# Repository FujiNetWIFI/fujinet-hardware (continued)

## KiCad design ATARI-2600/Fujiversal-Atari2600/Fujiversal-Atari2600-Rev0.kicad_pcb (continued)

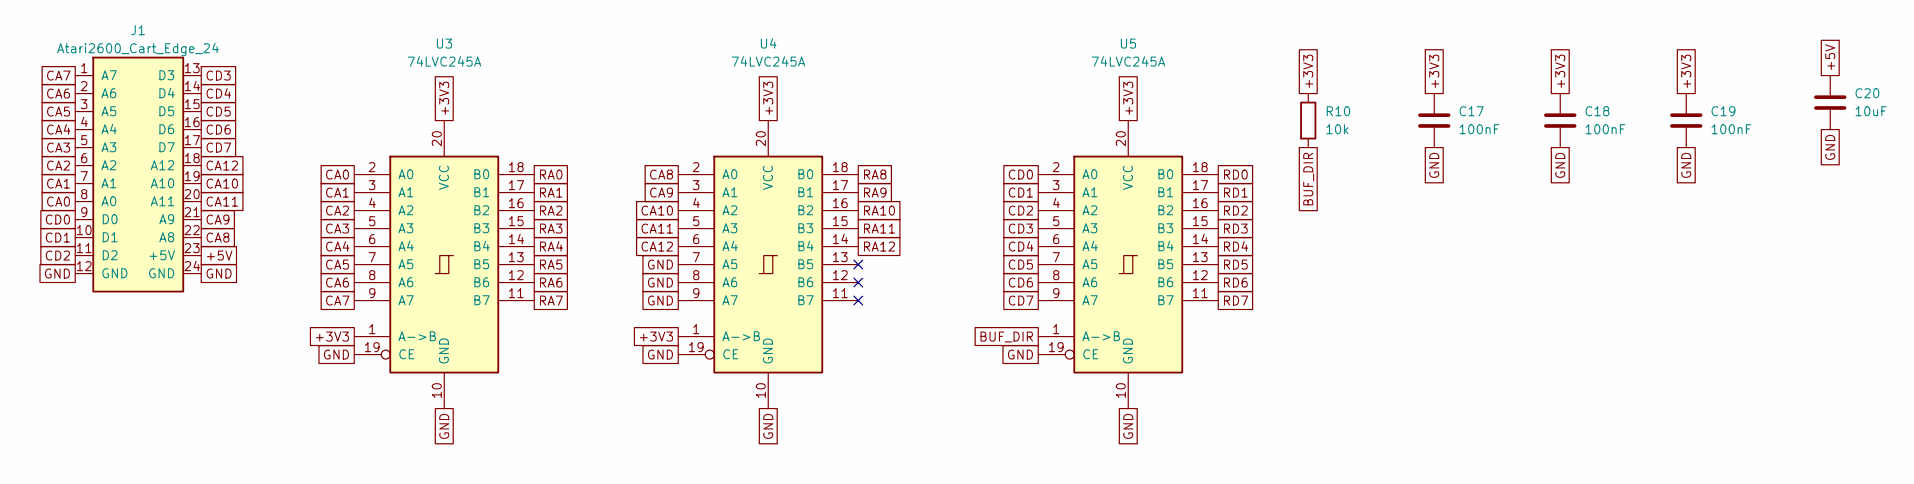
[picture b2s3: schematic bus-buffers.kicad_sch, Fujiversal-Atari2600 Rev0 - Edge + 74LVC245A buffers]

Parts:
C17, C18, C19: 100nF; C_0603_1608Metric; MPN CC0603KRX7R9BB104; LCSC C14663
C20: 10uF; C_0603_1608Metric; MPN CL10A106KP8NNNC; LCSC C19702
J1: Atari2600_Cart_Edge_24
R10: 10k; R_0603_1608Metric; MPN 0603WAF1002T5E; LCSC C25804
U3, U4, U5: 74LVC245A; TSSOP-20_4.4x6.5mm_P0.65mm; MPN 74LVC245APW,118; LCSC C6082

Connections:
+3V3: C17.1, C18.1, C19.1, R10.1, U3.1 (A->B), U3.20 (VCC), U4.1 (A->B), U4.20 (VCC), U5.20 (VCC); also elsewhere on the board
+5V: C20.1, J1.23 (+5V); also elsewhere on the board
BUF_DIR: R10.2, U5.1 (A->B); also elsewhere on the board
CA0: J1.8 (A0), U3.2 (A0)
CA1: J1.7 (A1), U3.3 (A1)
CA2: J1.6 (A2), U3.4 (A2)
CA3: J1.5 (A3), U3.5 (A3)
CA4: J1.4 (A4), U3.6 (A4)
CA5: J1.3 (A5), U3.7 (A5)
CA6: J1.2 (A6), U3.8 (A6)
CA7: J1.1 (A7), U3.9 (A7)
CA8: J1.22 (A8), U4.2 (A0)
CA9: J1.21 (A9), U4.3 (A1)
CA10: J1.19 (A10), U4.4 (A2)
CA11: J1.20 (A11), U4.5 (A3)
CA12: J1.18 (A12), U4.6 (A4)
CD0: J1.9 (D0), U5.2 (A0)
CD1: J1.10 (D1), U5.3 (A1)
CD2: J1.11 (D2), U5.4 (A2)
CD3: J1.13 (D3), U5.5 (A3)
CD4: J1.14 (D4), U5.6 (A4)
CD5: J1.15 (D5), U5.7 (A5)
CD6: J1.16 (D6), U5.8 (A6)
CD7: J1.17 (D7), U5.9 (A7)
GND: C17.2, C18.2, C19.2, C20.2, J1.12 (GND), J1.24 (GND), U3.10 (GND), U3.19 (CE), U4.7 (A5), U4.8 (A6), U4.9 (A7), U4.10 (GND), U4.19 (CE), U5.10 (GND), U5.19 (CE); also elsewhere on the board
RA0: U3.18 (B0); also elsewhere on the board
RA1: U3.17 (B1); also elsewhere on the board
RA2: U3.16 (B2); also elsewhere on the board
RA3: U3.15 (B3); also elsewhere on the board
RA4: U3.14 (B4); also elsewhere on the board
RA5: U3.13 (B5); also elsewhere on the board
RA6: U3.12 (B6); also elsewhere on the board
RA7: U3.11 (B7); also elsewhere on the board
RA8: U4.18 (B0); also elsewhere on the board
RA9: U4.17 (B1); also elsewhere on the board
RA10: U4.16 (B2); also elsewhere on the board
RA11: U4.15 (B3); also elsewhere on the board
RA12: U4.14 (B4); also elsewhere on the board
RD0: U5.18 (B0); also elsewhere on the board
RD1: U5.17 (B1); also elsewhere on the board
RD2: U5.16 (B2); also elsewhere on the board
RD3: U5.15 (B3); also elsewhere on the board
RD4: U5.14 (B4); also elsewhere on the board
RD5: U5.13 (B5); also elsewhere on the board
RD6: U5.12 (B6); also elsewhere on the board
RD7: U5.11 (B7); also elsewhere on the board

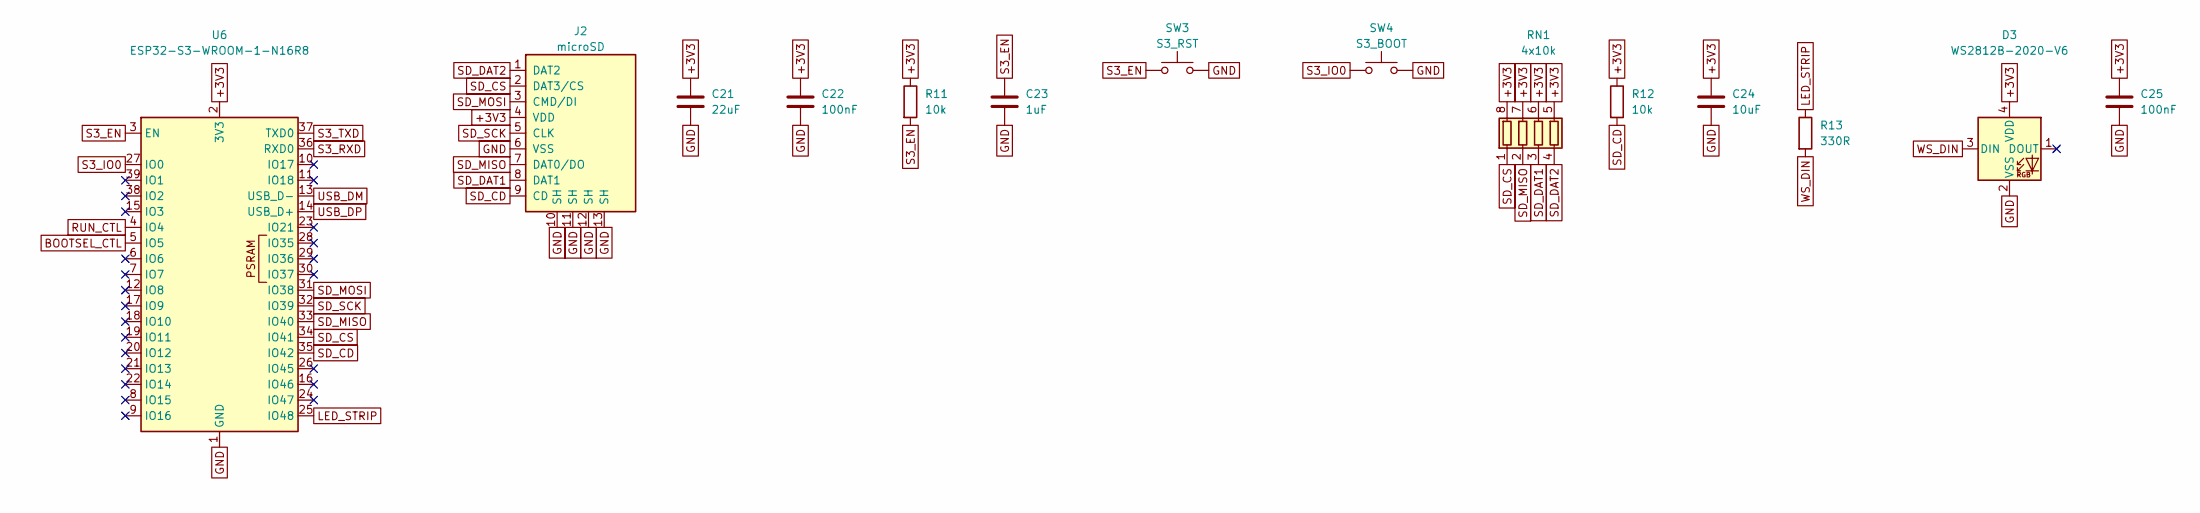
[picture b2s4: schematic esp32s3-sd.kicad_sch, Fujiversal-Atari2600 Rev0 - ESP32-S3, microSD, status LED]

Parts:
C21: 22uF; C_0805_2012Metric; MPN CL21A226MAQNNNE; LCSC C45783
C22, C25: 100nF; C_0603_1608Metric; MPN CC0603KRX7R9BB104; LCSC C14663
C23: 1uF; C_0603_1608Metric; MPN CL10A105KB8NNNC; LCSC C15849
C24: 10uF; C_0603_1608Metric; MPN CL10A106KP8NNNC; LCSC C19702
D3: WS2812B-2020-V6; LED_WS2812B-2020_PLCC4_2.0x2.0mm; MPN WS2812B-2020-V6; LCSC C52917434
J2: microSD; TF-SMD_TF-015; MPN TF-015; LCSC C113206
R11, R12: 10k; R_0603_1608Metric; MPN 0603WAF1002T5E; LCSC C25804
R13: 330R; R_0603_1608Metric; MPN 0603WAF3300T5E; LCSC C23138
RN1: 4x10k; R_Array_Convex_4x0603; MPN 4D03WGJ0103T5E; LCSC C29718
SW3: S3_RST; SW_SPST_TL3342; MPN TL3342F160QG; LCSC C2886898
SW4: S3_BOOT; SW_SPST_TL3342; MPN TL3342F160QG; LCSC C2886898
U6: ESP32-S3-WROOM-1-N16R8; ESP32-S3-WROOM-1; MPN ESP32-S3-WROOM-1-N16R8; LCSC C2913202

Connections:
+3V3: C21.1, C22.1, C24.1, C25.1, D3.4 (VDD), J2.4 (VDD), R11.1, R12.1, RN1.5 (R4.2), RN1.6 (R3.2), RN1.7 (R2.2), RN1.8 (R1.2), U6.2 (3V3); also elsewhere on the board
BOOTSEL_CTL: U6.5 (IO5); also elsewhere on the board
GND: C21.2, C22.2, C23.2, C24.2, C25.2, D3.2 (VSS), J2.6 (VSS), J2.10 (SH), J2.11 (SH), J2.12 (SH), J2.13 (SH), SW3.2, SW4.2, U6.1 (GND), U6.40 (GND), U6.41 (GND); also elsewhere on the board
LED_STRIP: R13.1, U6.25 (IO48)
RUN_CTL: U6.4 (IO4); also elsewhere on the board
S3_EN: C23.1, R11.2, SW3.1, U6.3 (EN); also elsewhere on the board
S3_IO0: SW4.1, U6.27 (IO0); also elsewhere on the board
S3_RXD: U6.36 (RXD0); also elsewhere on the board
S3_TXD: U6.37 (TXD0); also elsewhere on the board
SD_CD: J2.9 (CD), R12.2, U6.35 (IO42)
SD_CS: J2.2 (DAT3/CS), RN1.1 (R1.1), U6.34 (IO41)
SD_DAT1: J2.8 (DAT1), RN1.3 (R3.1)
SD_DAT2: J2.1 (DAT2), RN1.4 (R4.1)
SD_MISO: J2.7 (DAT0/DO), RN1.2 (R2.1), U6.33 (IO40)
SD_MOSI: J2.3 (CMD/DI), U6.31 (IO38)
SD_SCK: J2.5 (CLK), U6.32 (IO39)
USB_DM: U6.13 (USB_D-); also elsewhere on the board
USB_DP: U6.14 (USB_D+); also elsewhere on the board
WS_DIN: D3.3 (DIN), R13.2

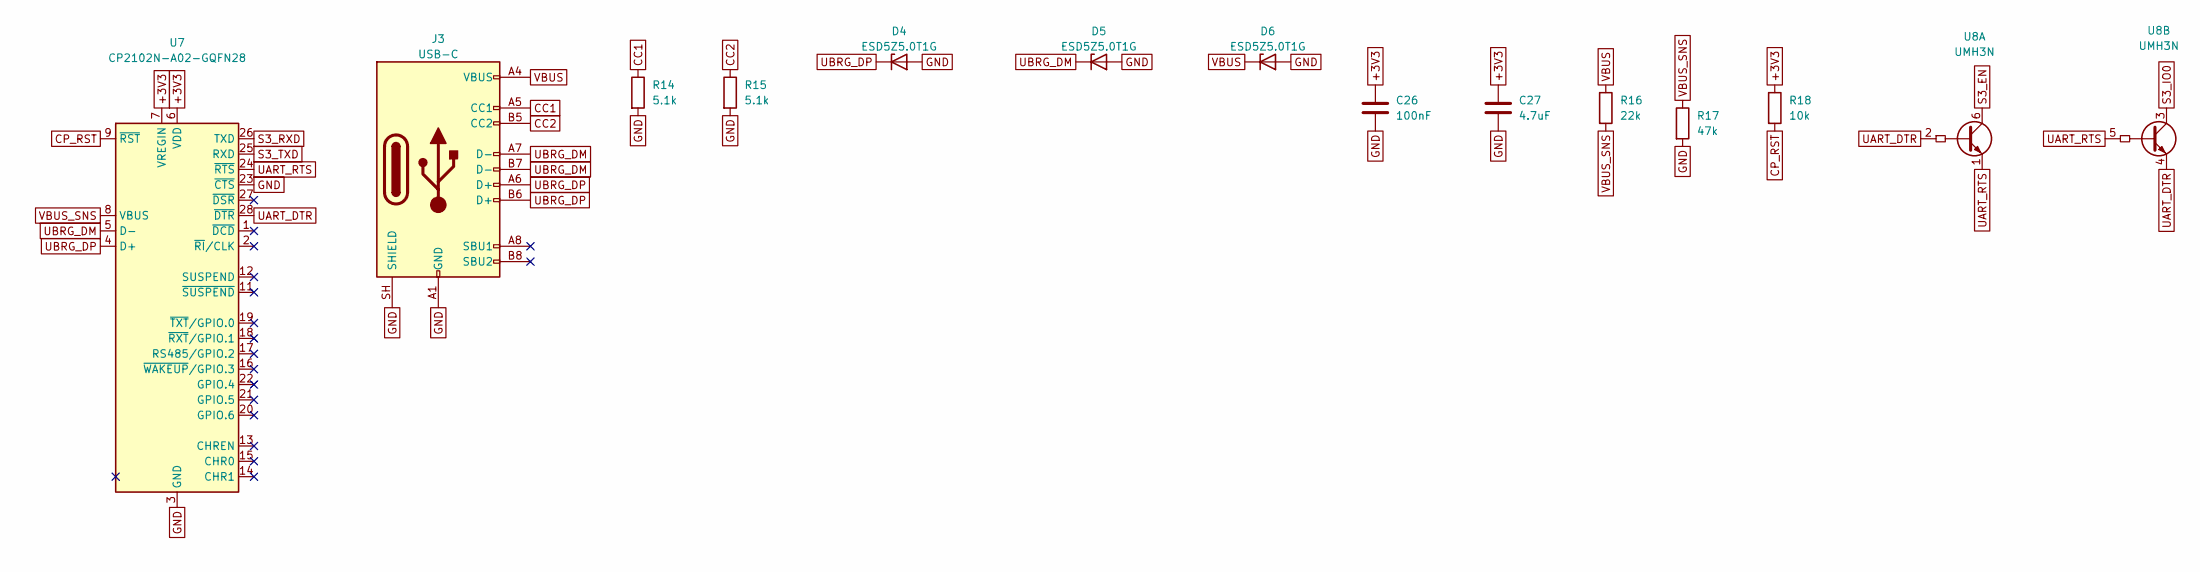
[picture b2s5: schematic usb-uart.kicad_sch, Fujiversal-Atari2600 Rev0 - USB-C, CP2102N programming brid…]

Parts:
C26: 100nF; C_0603_1608Metric; MPN CC0603KRX7R9BB104; LCSC C14663
C27: 4.7uF; C_0603_1608Metric; MPN CL10A475KO8NNNC; LCSC C19666
D4, D5, D6: ESD5Z5.0T1G; D_SOD-523; MPN ESD5Z5.0T1G; LCSC C82044
J3: USB-C; USB_C_Receptacle_HRO_TYPE-C-31-M-12; MPN TYPE-C-31-M-12; LCSC C165948
R14, R15: 5.1k; R_0603_1608Metric; MPN 0603WAF5101T5E; LCSC C23186
R16: 22k; R_0603_1608Metric; MPN 0603WAF2202T5E; LCSC C31850
R17: 47k; R_0603_1608Metric; MPN 0603WAF4702T5E; LCSC C25819
R18: 10k; R_0603_1608Metric; MPN 0603WAF1002T5E; LCSC C25804
U7: CP2102N-A02-GQFN28; QFN-28-1EP_5x5mm_P0.5mm_EP3.35x3.35mm; MPN CP2102N-A02-GQFN28R; LCSC C964632
U8: UMH3N; SOT-363_SC-70-6; MPN UMH3N; LCSC C62892

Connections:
+3V3: C26.1, C27.1, R18.1, U7.6 (VDD), U7.7 (VREGIN); also elsewhere on the board
CC1: J3.A5 (CC1), R14.1
CC2: J3.B5 (CC2), R15.1
CP_RST: R18.2, U7.9 (~RST)
GND: C26.2, C27.2, D4.2 (A), D5.2 (A), D6.2 (A), J3.A1 (GND), J3.A12 (GND), J3.B1 (GND), J3.B12 (GND), J3.SH (SHIELD), R14.2, R15.2, R17.2, U7.3 (GND), U7.23 (~CTS), U7.29 (GND); also elsewhere on the board
S3_EN: U8.6 (C1); also elsewhere on the board
S3_IO0: U8.3 (C2); also elsewhere on the board
S3_RXD: U7.26 (TXD); also elsewhere on the board
S3_TXD: U7.25 (RXD); also elsewhere on the board
UART_DTR: U7.28 (~DTR), U8.2 (B1), U8.4 (E2)
UART_RTS: U7.24 (~RTS), U8.1 (E1), U8.5 (B2)
UBRG_DM: D5.1 (K), J3.A7 (D-), J3.B7 (D-), U7.5 (D-)
UBRG_DP: D4.1 (K), J3.A6 (D+), J3.B6 (D+), U7.4 (D+)
VBUS: D6.1 (K), J3.A4 (VBUS), J3.A9 (VBUS), J3.B4 (VBUS), J3.B9 (VBUS), R16.1; also elsewhere on the board
VBUS_SNS: R16.2, R17.1, U7.8 (VBUS)

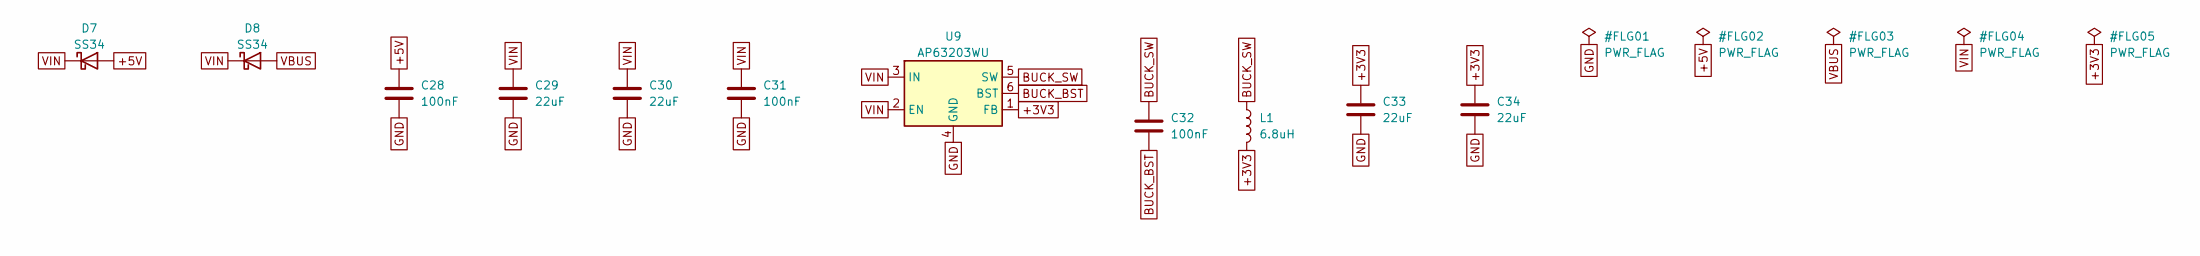
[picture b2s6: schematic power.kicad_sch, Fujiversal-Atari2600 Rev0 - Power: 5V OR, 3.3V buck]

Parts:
C28, C31, C32: 100nF; C_0603_1608Metric; MPN CC0603KRX7R9BB104; LCSC C14663
C29, C30, C33, C34: 22uF; C_0805_2012Metric; MPN CL21A226MAQNNNE; LCSC C45783
D7, D8: SS34; D_SMA; MPN SS34; LCSC C8678
L1: 6.8uH; L_Sunlord_SWPA4030S; MPN SWPA4030S6R8MT; LCSC C62684
U9: AP63203WU; TSOT-23-6; MPN AP63203WU-7; LCSC C780769

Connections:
+3V3: C33.1, C34.1, L1.2, U9.1 (FB); also elsewhere on the board
+5V: C28.1, D7.2 (A); also elsewhere on the board
BUCK_BST: C32.2, U9.6 (BST)
BUCK_SW: C32.1, L1.1, U9.5 (SW)
GND: C28.2, C29.2, C30.2, C31.2, C33.2, C34.2, U9.4 (GND); also elsewhere on the board
VBUS: D8.2 (A); also elsewhere on the board
VIN: C29.1, C30.1, C31.1, D7.1 (K), D8.1 (K), U9.2 (EN), U9.3 (IN)

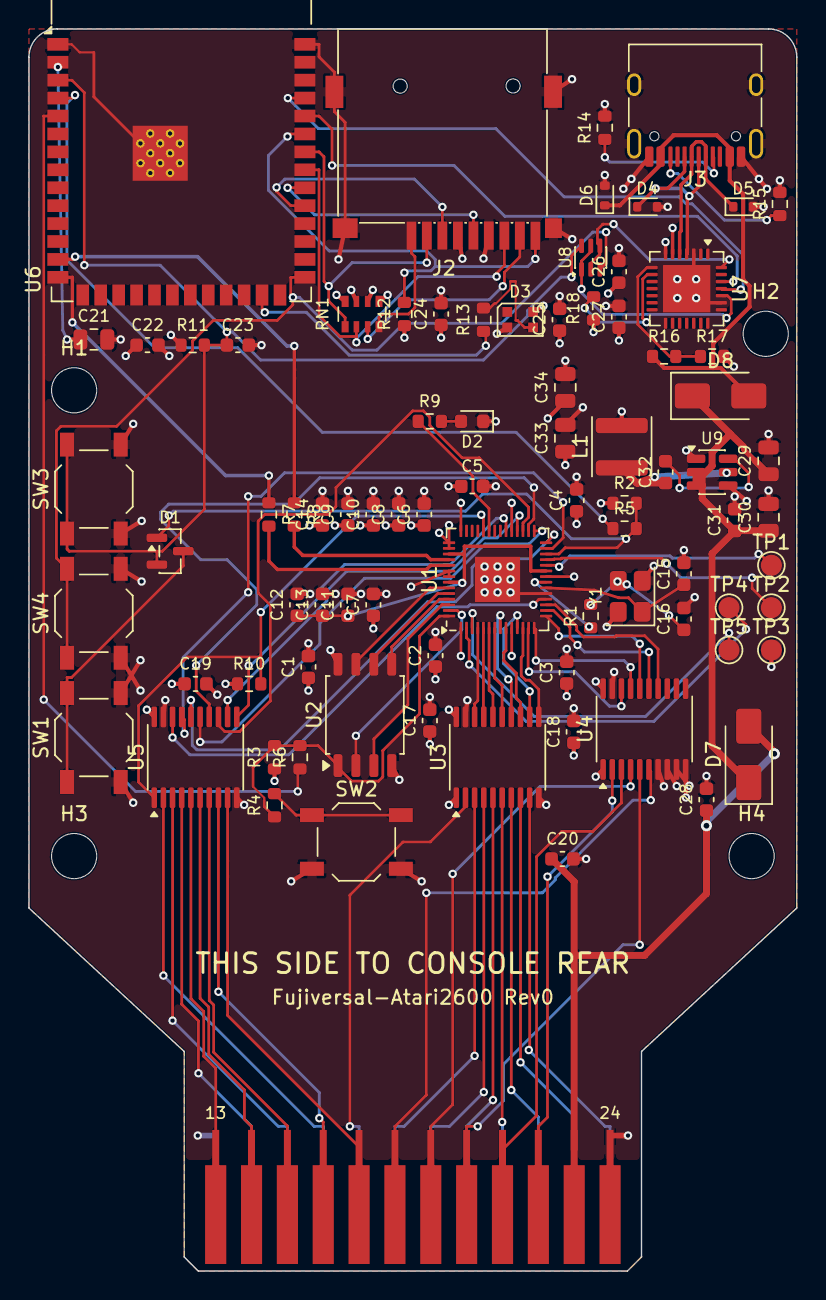
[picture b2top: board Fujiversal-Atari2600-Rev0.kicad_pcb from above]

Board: 4 copper layers, 54.4 x 88.0 mm, 88 parts (0 on the bottom side), 96 nets.

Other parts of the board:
H1, H2, H3, H4: M3; MountingHole_3.2mm_NPTH

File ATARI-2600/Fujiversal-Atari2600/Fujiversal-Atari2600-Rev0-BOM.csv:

"Refs","Value","Footprint","MPN","LCSC","Description","DNP"
"C1,C2,C3,C4,C5,C6,C7,C8,C9,C12,C13,C17,C18,C19,C22,C25,C26,C28,C31,C32","100nF","C_0603_1608Metric","CC0603KRX7R9BB104","C14663","flash VCC",""
"C10,C11,C23","1uF","C_0603_1608Metric","CL10A105KB8NNNC","C15849","VREG_VIN",""
"C14,C20,C24","10uF","C_0603_1608Metric","CL10A106KP8NNNC","C19702","RP 3V3 bulk",""
"C15,C16","15pF","C_0603_1608Metric","CL10C150JB8NNNC","C1644","crystal load",""
"C21,C29,C30,C33,C34","22uF","C_0805_2012Metric","CL21A226MAQNNNE","C45783","S3 bulk (WiFi TX bursts)",""
"C27","4.7uF","C_0603_1608Metric","CL10A475KO8NNNC","C19666","CP2102N VDD bulk",""
"D1","BAT54C","SOT-23","BAT54C,215","C37704","RESET steering, common cathode",""
"D2","green","LED_0603_1608Metric","KT-0603G","C12624","RP activity LED (GP25)",""
"D3","WS2812B-2020-V6","LED_WS2812B-2020_PLCC4_2.0x2.0mm","WS2812B-2020-V6","C52917434","status LED (3.3V-rated V6 part: no data-level shifting needed)",""
"D4,D5,D6","ESD5Z5.0T1G","D_SOD-523","ESD5Z5.0T1G","C82044","ESD",""
"D7,D8","SS34","D_SMA","SS34","C8678","console 5V OR-ing",""
"J2","microSD","TF-SMD_TF-015","TF-015","C113206","microSD push-push, SPI mode",""
"J3","USB-C","USB_C_Receptacle_HRO_TYPE-C-31-M-12","TYPE-C-31-M-12","C165948","power + S3 programming",""
"L1","6.8uH","L_Sunlord_SWPA4030S","SWPA4030S6R8MT","C62684","buck inductor",""
"R1,R4,R5,R6,R9","1k","R_0603_1608Metric","0603WAF1001T5E","C21190","crystal drive limit",""
"R2,R3,R10,R11,R12,R18","10k","R_0603_1608Metric","0603WAF1002T5E","C25804","RUN pull-up",""
"R7,R8","27R","R_0603_1608Metric","0603WAF270JT5E","C25190","USB series",""
"R13","330R","R_0603_1608Metric","0603WAF3300T5E","C23138","WS2812 data series",""
"R14,R15","5.1k","R_0603_1608Metric","0603WAF5101T5E","C23186","UFP Rd",""
"R16","22k","R_0603_1608Metric","0603WAF2202T5E","C31850","VBUS sense divider",""
"R17","47k","R_0603_1608Metric","0603WAF4702T5E","C25819","VBUS sense divider",""
"RN1","4x10k","R_Array_Convex_4x0603","4D03WGJ0103T5E","C29718","SD pull-ups",""
"SW1","RESET","SW_SPST_TL3342","TL3342F160QG","C2886898","cart RESET: RP RUN + S3 EN via BAT54C",""
"SW2","BOOTSEL","SW_SPST_TL3342","TL3342F160QG","C2886898","RP2040 BOOTSEL (hold while pressing RESET)",""
"SW3","S3_RST","SW_SPST_TL3342","TL3342F160QG","C2886898","ESP32-S3 EN",""
"SW4","S3_BOOT","SW_SPST_TL3342","TL3342F160QG","C2886898","ESP32-S3 BOOT (IO0)",""
"U1","RP2040","QFN-56-1EP_7x7mm_P0.4mm_EP3.2x3.2mm","RP2040","C2040","cartridge bus server (fujivcs)",""
"U2","W25Q16JVSSIQ","SOIC-8_5.3x5.3mm_P1.27mm","W25Q16JVSSIQ","C131025","2 MB QSPI flash (PICO_FLASH_SIZE_BYTES 2097152)",""
"U3,U4,U5","74LVC245A","TSSOP-20_4.4x6.5mm_P0.65mm","74LVC245APW,118","C6082","A0-A7 console -> RP (DIR high: A->B always)",""
"U6","ESP32-S3-WROOM-1-N16R8","ESP32-S3-WROOM-1","ESP32-S3-WROOM-1-N16R8","C2913202","FujiNet core (fujiversal-atari2600)",""
"U7","CP2102N-A02-GQFN28","QFN-28-1EP_5x5mm_P0.5mm_EP3.35x3.35mm","CP2102N-A02-GQFN28R","C964632","USB-UART for S3 flashing/console (self-powered)",""
"U8","UMH3N","SOT-363_SC-70-6","UMH3N","C62892","esptool auto-program (DevKitC-1 style)",""
"U9","AP63203WU","TSOT-23-6","AP63203WU-7","C780769","3.3V 2A buck",""
"Y1","12MHz","Crystal_SMD_3225-4Pin_3.2x2.5mm","ABM8-272-T3","C20625731","",""

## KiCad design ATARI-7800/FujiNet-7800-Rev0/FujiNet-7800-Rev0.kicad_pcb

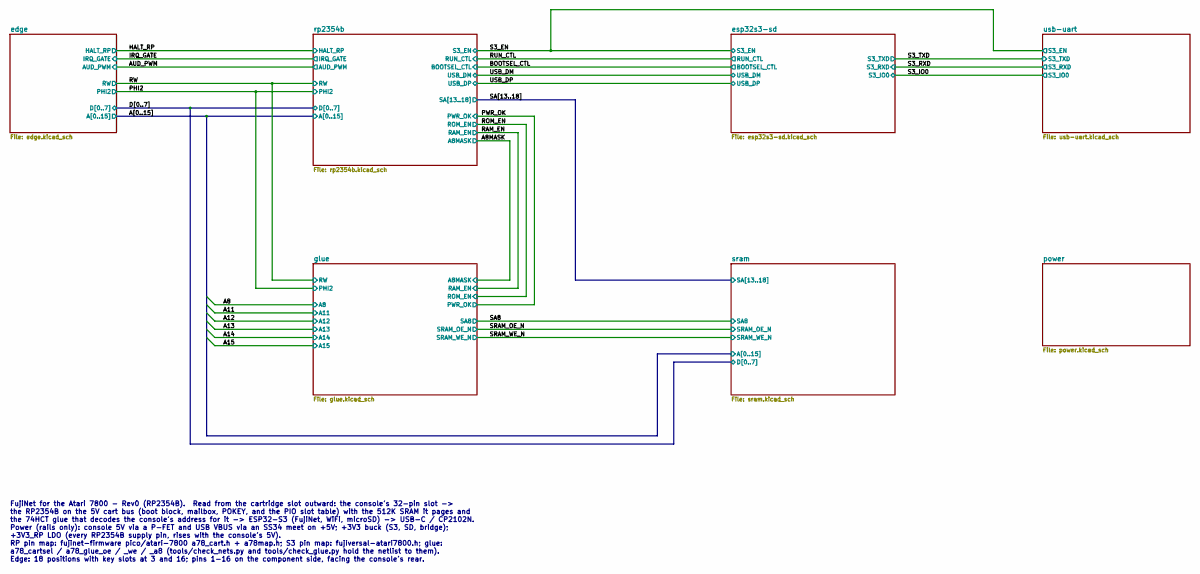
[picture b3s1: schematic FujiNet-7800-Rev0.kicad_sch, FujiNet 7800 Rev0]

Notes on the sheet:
FujiNet for the Atari 7800 - Rev0 (RP2354B). Read from the cartridge slot outward: the console's 32-pin slot -> the RP2354B on the 5V cart bus (boot block, mailbox, POKEY, and the PIO slot table) with the 512K SRAM it pages and the 74HCT glue that decodes the console's address for it -> ESP32-S3 (F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

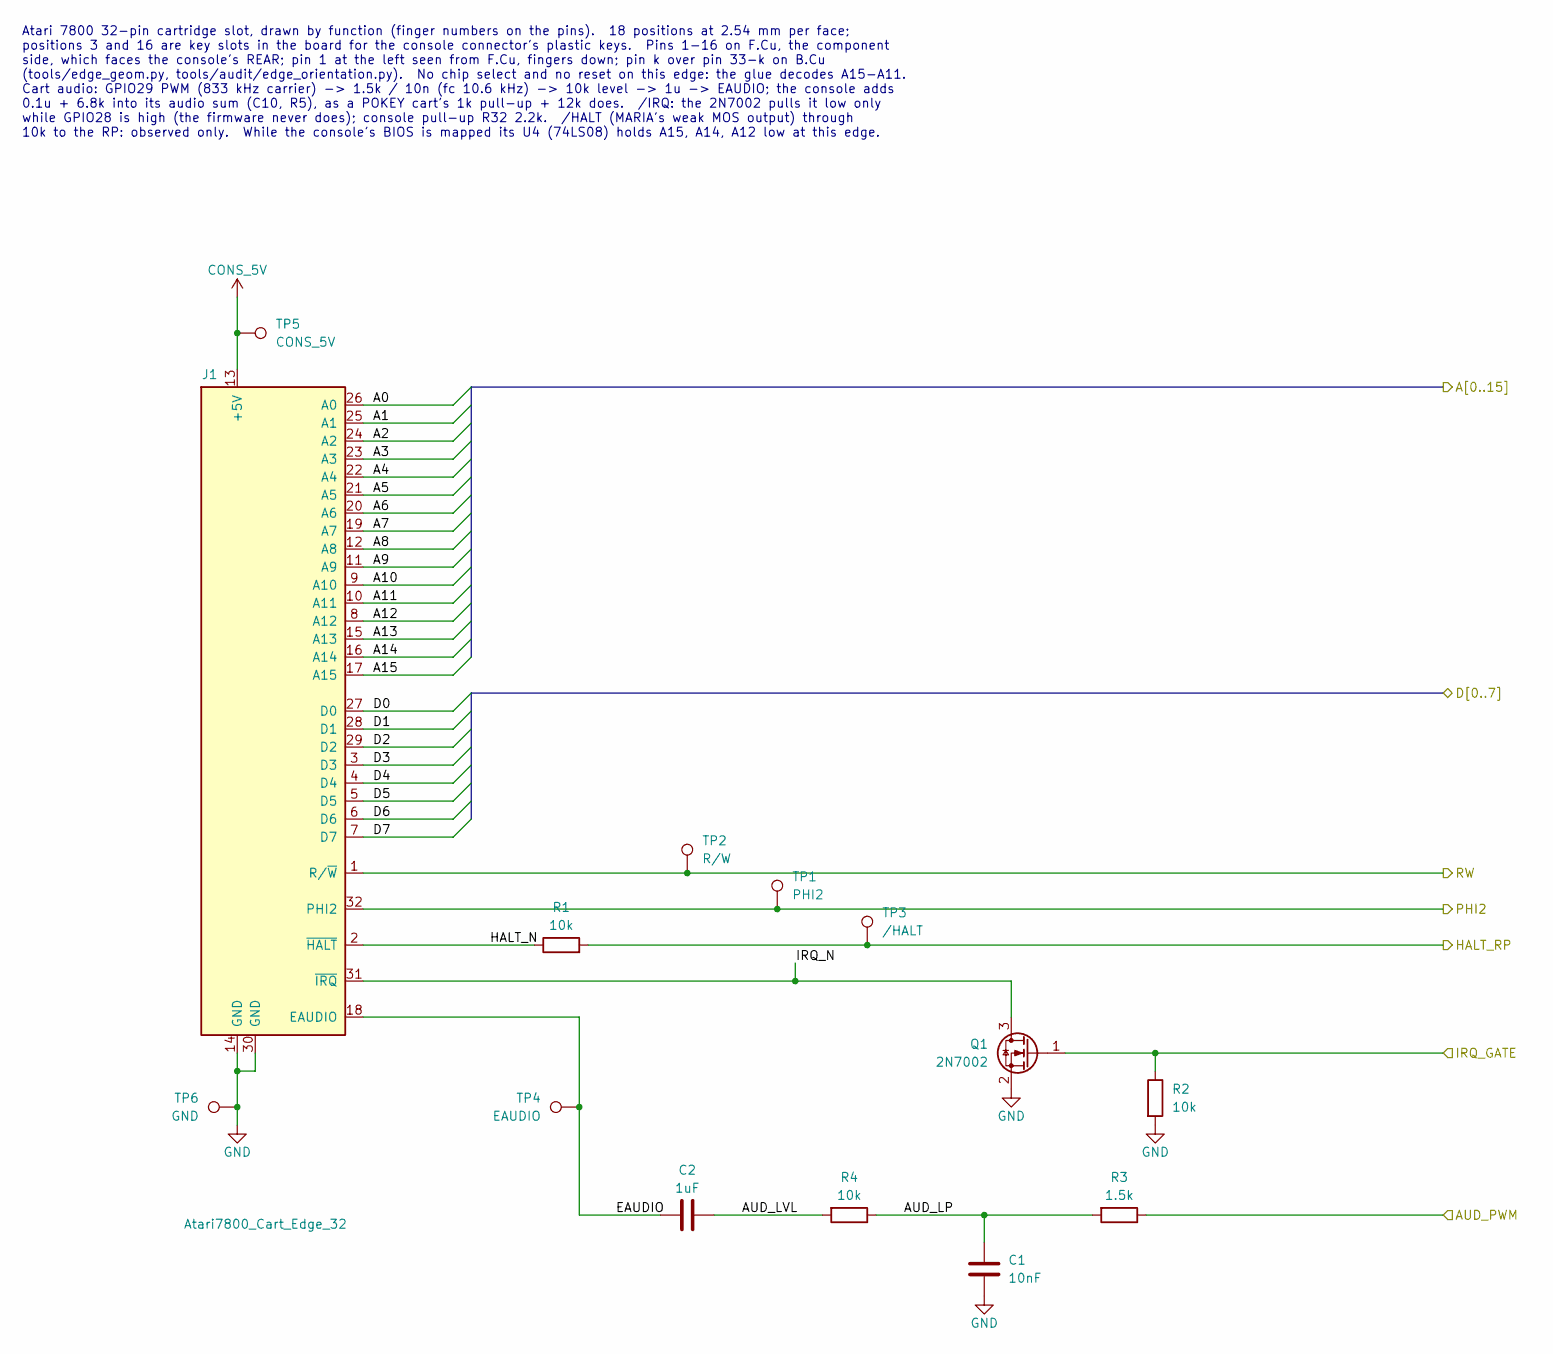
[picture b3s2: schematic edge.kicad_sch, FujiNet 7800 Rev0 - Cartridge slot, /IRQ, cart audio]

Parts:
C1: 10nF; C_0603_1608Metric; MPN 0603B103K500NT; LCSC C57112
C2: 1uF; C_0603_1608Metric; MPN CL10A105KB8NNNC; LCSC C15849
J1: Atari7800_Cart_Edge_32
Q1: 2N7002; SOT-23; MPN 2N7002; LCSC C8545
R1, R2, R4: 10k; R_0603_1608Metric; MPN 0603WAF1002T5E; LCSC C25804
R3: 1.5k; R_0603_1608Metric; MPN 0603WAF1501T5E; LCSC C22843
TP1: PHI2; TestPoint_Pad_D1.5mm
TP2: R/W; TestPoint_Pad_D1.5mm
TP3: /HALT; TestPoint_Pad_D1.5mm
TP4: EAUDIO; TestPoint_Pad_D1.5mm
TP5: CONS_5V; TestPoint_Pad_D1.5mm
TP6: GND; TestPoint_Pad_D1.5mm

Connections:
/A0: J1.26 (A0); also elsewhere on the board
/A1: J1.25 (A1); also elsewhere on the board
/A2: J1.24 (A2); also elsewhere on the board
/A3: J1.23 (A3); also elsewhere on the board
/A4: J1.22 (A4); also elsewhere on the board
/A5: J1.21 (A5); also elsewhere on the board
/A6: J1.20 (A6); also elsewhere on the board
/A7: J1.19 (A7); also elsewhere on the board
/A8: J1.12 (A8); also elsewhere on the board
/A9: J1.11 (A9); also elsewhere on the board
/A10: J1.9 (A10); also elsewhere on the board
/A11: J1.10 (A11); also elsewhere on the board
/A12: J1.8 (A12); also elsewhere on the board
/A13: J1.15 (A13); also elsewhere on the board
/A14: J1.16 (A14); also elsewhere on the board
/A15: J1.17 (A15); also elsewhere on the board
/AUD_PWM: R3.1; also elsewhere on the board
/D0: J1.27 (D0); also elsewhere on the board
/D1: J1.28 (D1); also elsewhere on the board
/D2: J1.29 (D2); also elsewhere on the board
/D3: J1.3 (D3); also elsewhere on the board
/D4: J1.4 (D4); also elsewhere on the board
/D5: J1.5 (D5); also elsewhere on the board
/D6: J1.6 (D6); also elsewhere on the board
/D7: J1.7 (D7); also elsewhere on the board
/HALT_RP: R1.2, TP3.1; also elsewhere on the board
/IRQ_GATE: Q1.1 (G), R2.1; also elsewhere on the board
/PHI2: J1.32 (PHI2), TP1.1; also elsewhere on the board
/RW: J1.1 (R/~W), TP2.1; also elsewhere on the board
/edge/AUD_LP: C1.1, R3.2, R4.1
/edge/AUD_LVL: C2.1, R4.2
/edge/EAUDIO: C2.2, J1.18 (EAUDIO), TP4.1
/edge/HALT_N: J1.2 (~HALT), R1.1
/edge/IRQ_N: J1.31 (~IRQ), Q1.3 (D)
CONS_5V: J1.13 (+5V), TP5.1; also elsewhere on the board
GND: C1.2, J1.14 (GND), J1.30 (GND), Q1.2 (S), R2.2, TP6.1; also elsewhere on the board

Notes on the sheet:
Atari 7800 32-pin cartridge slot, drawn by function (finger numbers on the pins). 18 positions at 2.54 mm per face; positions 3 and 16 are key slots in the board for the console connector's plastic keys. Pins 1-16 on F.Cu, the component side, which faces the console's REAR; pin 1 at the left seen f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

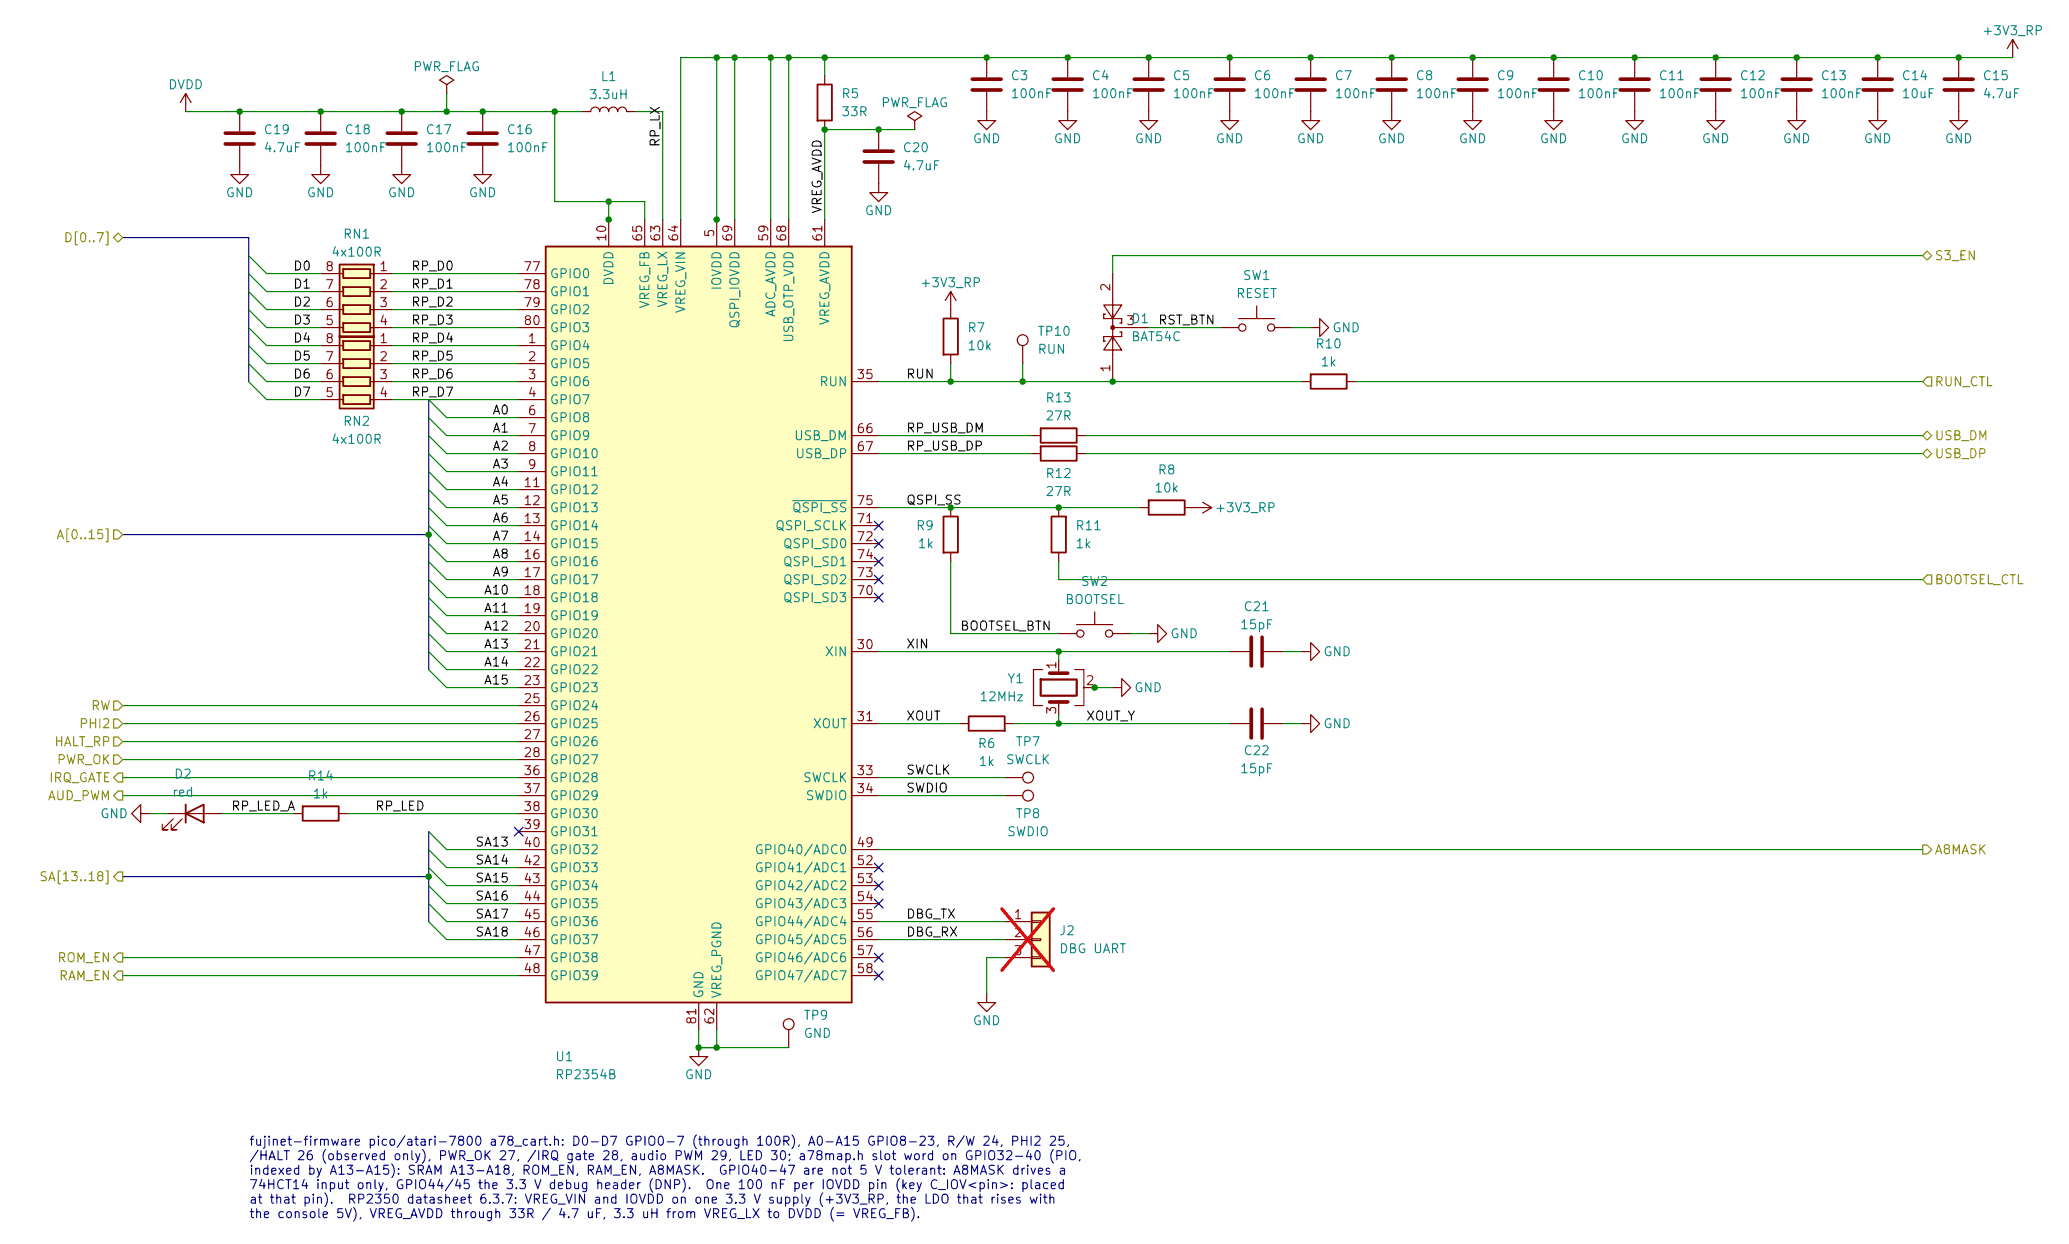
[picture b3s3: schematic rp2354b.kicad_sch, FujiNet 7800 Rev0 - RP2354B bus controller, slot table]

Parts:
C3, C4, C5, C6, C7, C8, C9, C10, C11, C12, C13, C16, C17, C18: 100nF; C_0603_1608Metric; MPN CC0603KRX7R9BB104; LCSC C14663
C14: 10uF; C_0603_1608Metric; MPN CL10A106KP8NNNC; LCSC C19702
C15, C19, C20: 4.7uF; C_0603_1608Metric; MPN CL10A475KO8NNNC; LCSC C19666
C21, C22: 15pF; C_0603_1608Metric; MPN CL10C150JB8NNNC; LCSC C1644
D1: BAT54C; SOT-23; MPN BAT54C,215; LCSC C37704
D2: red; LED_0603_1608Metric; MPN KT-0603R; LCSC C2286
J2: DBG UART; PinHeader_1x03_P2.54mm_Vertical; MPN PZ254V-11-03P; LCSC C2937625; not fitted
L1: 3.3uH; RPI_L_AOTA-B201610S3R3; MPN AOTA-B201610S3R3-101-T; LCSC C42411119
R5: 33R; R_0603_1608Metric; MPN 0603WAF330JT5E; LCSC C23140
R6, R9, R10, R11, R14: 1k; R_0603_1608Metric; MPN 0603WAF1001T5E; LCSC C21190
R7, R8: 10k; R_0603_1608Metric; MPN 0603WAF1002T5E; LCSC C25804
R12, R13: 27R; R_0603_1608Metric; MPN 0603WAF270JT5E; LCSC C25190
RN1, RN2: 4x100R; R_Array_Convex_4x0603; MPN 4D03WGJ0101T5E; LCSC C25506
SW1: RESET; SW_SPST_TS-1187A; MPN TS-1187A-B-A-B; LCSC C318884
SW2: BOOTSEL; SW_SPST_TS-1187A; MPN TS-1187A-B-A-B; LCSC C318884
TP7: SWCLK; TestPoint_Pad_D1.5mm
TP8: SWDIO; TestPoint_Pad_D1.5mm
TP9: GND; TestPoint_Pad_D1.5mm
TP10: RUN; TestPoint_Pad_D1.5mm
U1: RP2354B; QFN-80-1EP_10x10mm_P0.4mm_EP3.4x3.4mm; MPN RP2354B; LCSC C39843328
Y1: 12MHz; Crystal_SMD_3225-4Pin_3.2x2.5mm; MPN ABM8-272-T3; LCSC C20625731

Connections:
+3V3_RP: C3.1, C4.1, C5.1, C6.1, C7.1, C8.1, C9.1, C10.1, C11.1, C12.1, C13.1, C14.1, C15.1, R5.1, R7.1, R8.1, U1.5 (IOVDD), U1.15 (IOVDD), U1.24 (IOVDD), U1.29 (IOVDD), U1.41 (IOVDD), U1.50 (IOVDD), U1.59 (ADC_AVDD), U1.60 (IOVDD), U1.64 (VREG_VIN), U1.68 (USB_OTP_VDD), U1.69 (QSPI_IOVDD), U1.76 (IOVDD); also elsewhere on the board
/A0: U1.6 (GPIO8); also elsewhere on the board
/A1: U1.7 (GPIO9); also elsewhere on the board
/A2: U1.8 (GPIO10); also elsewhere on the board
/A3: U1.9 (GPIO11); also elsewhere on the board
/A4: U1.11 (GPIO12); also elsewhere on the board
/A5: U1.12 (GPIO13); also elsewhere on the board
/A6: U1.13 (GPIO14); also elsewhere on the board
/A7: U1.14 (GPIO15); also elsewhere on the board
/A8: U1.16 (GPIO16); also elsewhere on the board
/A8MASK: U1.49 (GPIO40/ADC0); also elsewhere on the board
/A9: U1.17 (GPIO17); also elsewhere on the board
/A10: U1.18 (GPIO18); also elsewhere on the board
/A11: U1.19 (GPIO19); also elsewhere on the board
/A12: U1.20 (GPIO20); also elsewhere on the board
/A13: U1.21 (GPIO21); also elsewhere on the board
/A14: U1.22 (GPIO22); also elsewhere on the board
/A15: U1.23 (GPIO23); also elsewhere on the board
/AUD_PWM: U1.37 (GPIO29); also elsewhere on the board
/BOOTSEL_CTL: R11.1; also elsewhere on the board
/D0: RN1.8 (R1.2); also elsewhere on the board
/D1: RN1.7 (R2.2); also elsewhere on the board
/D2: RN1.6 (R3.2); also elsewhere on the board
/D3: RN1.5 (R4.2); also elsewhere on the board
/D4: RN2.8 (R1.2); also elsewhere on the board
/D5: RN2.7 (R2.2); also elsewhere on the board
/D6: RN2.6 (R3.2); also elsewhere on the board
/D7: RN2.5 (R4.2); also elsewhere on the board
/HALT_RP: U1.27 (GPIO26); also elsewhere on the board
/IRQ_GATE: U1.36 (GPIO28); also elsewhere on the board
/PHI2: U1.26 (GPIO25); also elsewhere on the board
/PWR_OK: U1.28 (GPIO27); also elsewhere on the board
/RAM_EN: U1.48 (GPIO39); also elsewhere on the board
/ROM_EN: U1.47 (GPIO38); also elsewhere on the board
/RUN_CTL: R10.1; also elsewhere on the board
/RW: U1.25 (GPIO24); also elsewhere on the board
/S3_EN: D1.2; also elsewhere on the board
/SA13: U1.40 (GPIO32); also elsewhere on the board
/SA14: U1.42 (GPIO33); also elsewhere on the board
/SA15: U1.43 (GPIO34); also elsewhere on the board
/SA16: U1.44 (GPIO35); also elsewhere on the board
/SA17: U1.45 (GPIO36); also elsewhere on the board
/SA18: U1.46 (GPIO37); also elsewhere on the board
/USB_DM: R13.1; also elsewhere on the board
/USB_DP: R12.1; also elsewhere on the board
/rp2354b/BOOTSEL_BTN: R9.2, SW2.1
/rp2354b/DBG_RX: J2.2, U1.56 (GPIO45/ADC5)
/rp2354b/DBG_TX: J2.1, U1.55 (GPIO44/ADC4)
/rp2354b/QSPI_SS: R8.2, R9.1, R11.2, U1.75 (~QSPI_SS)
/rp2354b/RP_D0: RN1.1 (R1.1), U1.77 (GPIO0)
/rp2354b/RP_D1: RN1.2 (R2.1), U1.78 (GPIO1)
/rp2354b/RP_D2: RN1.3 (R3.1), U1.79 (GPIO2)
/rp2354b/RP_D3: RN1.4 (R4.1), U1.80 (GPIO3)
/rp2354b/RP_D4: RN2.1 (R1.1), U1.1 (GPIO4)
/rp2354b/RP_D5: RN2.2 (R2.1), U1.2 (GPIO5)
/rp2354b/RP_D6: RN2.3 (R3.1), U1.3 (GPIO6)
/rp2354b/RP_D7: RN2.4 (R4.1), U1.4 (GPIO7)
/rp2354b/RP_LED: R14.1, U1.38 (GPIO30)
/rp2354b/RP_LED_A: D2.2 (A), R14.2
/rp2354b/RP_LX: L1.2, U1.63 (VREG_LX)
/rp2354b/RP_USB_DM: R13.2, U1.66 (USB_DM)
/rp2354b/RP_USB_DP: R12.2, U1.67 (USB_DP)
/rp2354b/RST_BTN: D1.3, SW1.1
/rp2354b/RUN: D1.1, R7.2, R10.2, TP10.1, U1.35 (RUN)
/rp2354b/SWCLK: TP7.1, U1.33 (SWCLK)
/rp2354b/SWDIO: TP8.1, U1.34 (SWDIO)
/rp2354b/VREG_AVDD: C20.1, R5.2, U1.61 (VREG_AVDD)
/rp2354b/XIN: C21.1, U1.30 (XIN), Y1.1
/rp2354b/XOUT: R6.1, U1.31 (XOUT)
/rp2354b/XOUT_Y: C22.1, R6.2, Y1.3
DVDD: C16.1, C17.1, C18.1, C19.1, L1.1, U1.10 (DVDD), U1.32 (DVDD), U1.51 (DVDD), U1.65 (VREG_FB)
GND: C3.2, C4.2, C5.2, C6.2, C7.2, C8.2, C9.2, C10.2, C11.2, C12.2, C13.2, C14.2, C15.2, C16.2, C17.2, C18.2, C19.2, C20.2, C21.2, C22.2, D2.1 (K), J2.3, SW1.2, SW2.2, TP9.1, U1.62 (VREG_PGND), U1.81 (GND), Y1.2 (G), Y1.4 (G); also elsewhere on the board

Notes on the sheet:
fujinet-firmware pico/atari-7800 a78_cart.h: D0-D7 GPIO0-7 (through 100R), A0-A15 GPIO8-23, R/W 24, PHI2 25, /HALT 26 (observed only), PWR_OK 27, /IRQ gate 28, audio PWM 29, LED 30; a78map.h slot word on GPIO32-40 (PIO, indexed by A13-A15): SRAM A13-A18, ROM_EN, RAM_EN, A8MASK. GPIO40-47 are not 5 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
